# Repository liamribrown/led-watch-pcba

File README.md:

# LED analogue watch PCBA

A wristwatch board that shows the time like an analogue watch, with LEDs in place of hands.
It stays dark until you press a button or tilt your wrist, then shows the time for about 5 seconds.

- **Board:** round, 38 mm, 4 layers, 1.0 mm. 60 amber 0402 LEDs on the outer ring (minutes) and
  12 red 0603 LEDs on the inner ring (hours), charlieplexed from 9 pins of an ATtiny3217.
  CR2032 coin cell, 32.768 kHz crystal for the clock, LIS2DH12 accelerometer for tilt-to-wake,
  two side buttons. Designed in KiCad 9 and generated from Python.
- **Firmware:** C for the ATtiny3217 (the pin-compatible ATtiny1617 also fits), with host unit tests.
- **Simulator:** a 3D model of the board plus a working watch that runs the real firmware logic
  compiled to WebAssembly: https://ai.liambrown.uk/watch/

## Status

Designed and reviewed on paper, **not yet built or tested on hardware.** Don't order boards
you aren't prepared to debug. Open points are in `projects/led-watch/SPEC.md` ("As built" and
the review tables at the end) and in `docs/reviews/`.

## Layout

| Path | What |
|---|---|
| `projects/led-watch/SPEC.md` | Requirements, decisions, as-built notes, BOM with LCSC parts |
| `projects/led-watch/PINMAP.md` | Pin map and LED table (the source of truth for firmware) |
| `projects/led-watch/tools/` | Python that generates the schematic and board (`generate.py`), plus the coin-cell safety check |
| `projects/led-watch/led-watch.kicad_*` | Generated KiCad project |
| `projects/led-watch/export.sh` | ERC/DRC gate, then gerbers, JLCPCB BOM and placement files |
| `projects/led-watch/firmware/` | Firmware, tests, build and flash scripts (see its README) |
| `projects/watch-sim/` | The browser simulator |
| `docs/led-watch-schematic.pdf` | Schematic (A3, one sheet, generated from the KiCad file) |
| `docs/reviews/` | Independent design reviews of the spec and board |

## Build it

```bash
# Board: needs KiCad 9 (kicad-cli). Stops on any ERC/DRC or coin-cell check failure.
projects/led-watch/export.sh

# Firmware: needs gcc (host tests) and avr-gcc.
cd projects/led-watch/firmware && ./build.sh
```

## Notes

- **Coin cell:** the board has a copper keep-out under the cell, enforced by
  `tools/check_cell.py`. Order plugged (filled) vias. 3.3 V SerialUPDI adapters only: a 5 V one
  would push current into the cell. In a case, the cell should only be reachable with a tool.
- **Cost (JLCPCB quote, 2026-11-12):** 10 assembled boards, both sides, about US$231 before
  shipping. Check part rotations in JLCPCB's placement preview before paying.
- **Stock:** the ATtiny3217 and the B3U-3100P buttons were low in stock on LCSC when the BOM
  was checked. The ATtiny1617 is the fallback chip.
- The documents were written by a small team of AI agents working under one person's direction,
  so they refer to "000" (the human) and agent numbers (003 Hardware, 004 Firmware, 007 Review).

## Licence

Software (firmware, simulator, generator scripts): **MIT**. Hardware design and documents:
**CERN-OHL-P-2.0**. Which folder is which is in [`LICENSE`](LICENSE); the texts are in `LICENSES/`.

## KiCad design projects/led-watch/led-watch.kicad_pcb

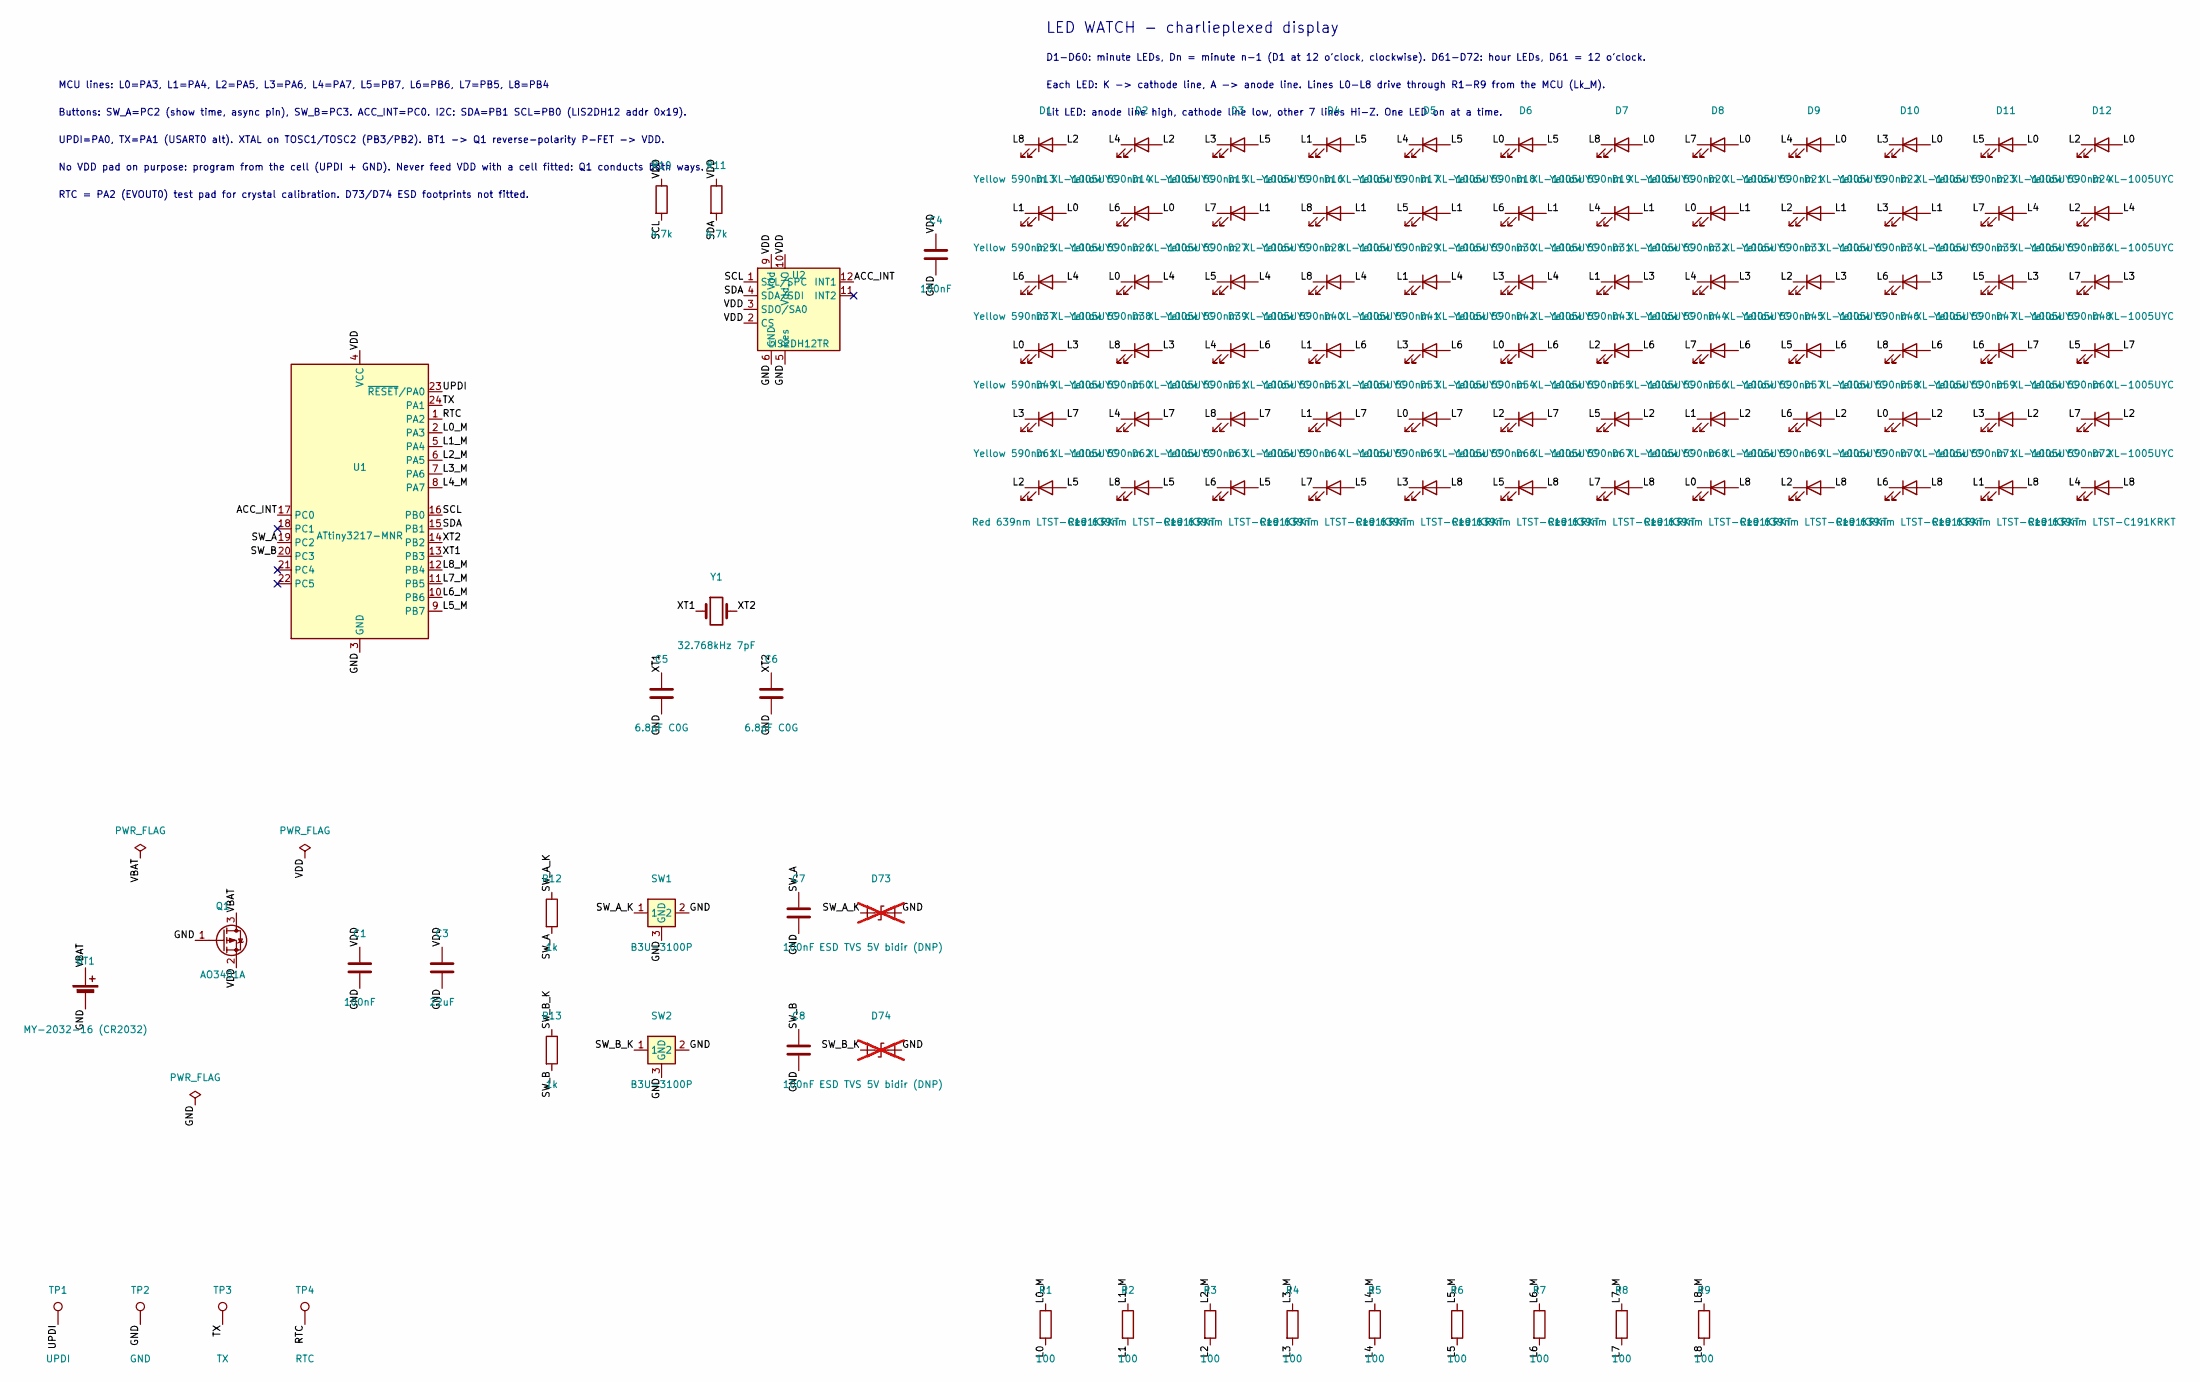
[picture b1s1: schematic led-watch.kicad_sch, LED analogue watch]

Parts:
BT1: MY-2032-16 (CR2032); BatteryHolder_MYOUNG_MY-2032-16; LCSC C2902340
C1, C4, C7, C8: 100nF; C_0402_1005Metric; LCSC C1525
C3: 22uF; C_0805_2012Metric; LCSC C45783
C5, C6: 6.8pF C0G; C_0402_1005Metric; LCSC C1576
D1, D2, D3, D4, D5, D6, D7, D8, D9, D10, D11, D12, D13, D14, D15, D16, D17, D18, D19, D20, D21, D22, D23, D24, D25, D26, D27, D28, D29, D30, D31, D32, D33, D34, D35, D36, D37, D38, D39, D40, D41, D42, D43, D44, D45, D46, D47, D48, D49, D50, D51, D52, D53, D54, D55, D56, D57, D58, D59, D60: Yellow 590nm XL-1005UYC; LED_0402_1005Metric_Tight; LCSC C25503856
D61, D62, D63, D64, D65, D66, D67, D68, D69, D70, D71, D72: Red 639nm LTST-C191KRKT; LED_0603_1608Metric; LCSC C125099
D73, D74: ESD TVS 5V bidir (DNP); D_0402_1005Metric; not fitted
Q1: AO3401A; SOT-23; LCSC C15127
R1, R2, R3, R4, R5, R6, R7, R8, R9: 100; R_0402_1005Metric; LCSC C25076
R10, R11: 4.7k; R_0402_1005Metric; LCSC C25900
R12, R13: 1k; R_0402_1005Metric; LCSC C11702
SW1, SW2: B3U-3100P; SW_SPST_B3U-3100P; LCSC C6748648
TP1: UPDI; TestPoint_Pad_D1.0mm
TP2: GND; TestPoint_Pad_D1.0mm
TP3: TX; TestPoint_Pad_D1.0mm
TP4: RTC; TestPoint_Pad_D1.0mm
U1: ATtiny3217-MNR; QFN-24-1EP_4x4mm_P0.5mm_EP2.6x2.6mm; LCSC C614177
U2: LIS2DH12TR; LGA-12_2x2mm_P0.5mm; LCSC C110926
Y1: 32.768kHz 7pF; Crystal_SMD_2012-2Pin_2.0x1.2mm; LCSC C5136974

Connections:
/ACC_INT: U1.17 (PC0), U2.12 (INT1)
/GND: BT1.2 (-), C1.2, C3.2, C4.2, C5.2, C6.2, C7.2, C8.2, D73.2 (A2), D74.2 (A2), Q1.1 (G), SW1.2, SW1.3 (GND), SW2.2, SW2.3 (GND), TP2.1, U1.3 (GND), U1.25 (GND), U2.5 (Res), U2.6 (GND), U2.7 (GND), U2.8 (GND)
/L0: D6.1 (K), D7.2 (A), D8.2 (A), D9.2 (A), D10.2 (A), D11.2 (A), D12.2 (A), D13.2 (A), D14.2 (A), D20.1 (K), D26.1 (K), D37.1 (K), D42.1 (K), D53.1 (K), D58.1 (K), D68.1 (K), R1.2
/L0_M: R1.1, U1.2 (PA3)
/L1: D4.1 (K), D13.1 (K), D15.2 (A), D16.2 (A), D17.2 (A), D18.2 (A), D19.2 (A), D20.2 (A), D21.2 (A), D22.2 (A), D29.1 (K), D31.1 (K), D40.1 (K), D52.1 (K), D56.1 (K), D71.1 (K), R2.2
/L1_M: R2.1, U1.5 (PA4)
/L2: D1.2 (A), D2.2 (A), D12.1 (K), D21.1 (K), D24.1 (K), D33.1 (K), D43.1 (K), D54.1 (K), D55.2 (A), D56.2 (A), D57.2 (A), D58.2 (A), D59.2 (A), D60.2 (A), D61.1 (K), D69.1 (K), R3.2
/L2_M: R3.1, U1.6 (PA5)
/L3: D3.1 (K), D10.1 (K), D22.1 (K), D30.1 (K), D31.2 (A), D32.2 (A), D33.2 (A), D34.2 (A), D35.2 (A), D36.2 (A), D37.2 (A), D38.2 (A), D41.1 (K), D49.1 (K), D59.1 (K), D65.1 (K), R4.2
/L3_M: R4.1, U1.7 (PA6)
/L4: D2.1 (K), D5.1 (K), D9.1 (K), D19.1 (K), D23.2 (A), D24.2 (A), D25.2 (A), D26.2 (A), D27.2 (A), D28.2 (A), D29.2 (A), D30.2 (A), D32.1 (K), D39.1 (K), D50.1 (K), D72.1 (K), R5.2
/L4_M: R5.1, U1.8 (PA7)
/L5: D3.2 (A), D4.2 (A), D5.2 (A), D6.2 (A), D11.1 (K), D17.1 (K), D27.1 (K), D35.1 (K), D45.1 (K), D48.1 (K), D55.1 (K), D61.2 (A), D62.2 (A), D63.2 (A), D64.2 (A), D66.1 (K), R6.2
/L5_M: R6.1, U1.9 (PB7)
/L6: D14.1 (K), D18.1 (K), D25.1 (K), D34.1 (K), D39.2 (A), D40.2 (A), D41.2 (A), D42.2 (A), D43.2 (A), D44.2 (A), D45.2 (A), D46.2 (A), D47.1 (K), D57.1 (K), D63.1 (K), D70.1 (K), R7.2
/L6_M: R7.1, U1.10 (PB6)
/L7: D8.1 (K), D15.1 (K), D23.1 (K), D36.1 (K), D44.1 (K), D47.2 (A), D48.2 (A), D49.2 (A), D50.2 (A), D51.2 (A), D52.2 (A), D53.2 (A), D54.2 (A), D60.1 (K), D64.1 (K), D67.1 (K), R8.2
/L7_M: R8.1, U1.11 (PB5)
/L8: D1.1 (K), D7.1 (K), D16.1 (K), D28.1 (K), D38.1 (K), D46.1 (K), D51.1 (K), D62.1 (K), D65.2 (A), D66.2 (A), D67.2 (A), D68.2 (A), D69.2 (A), D70.2 (A), D71.2 (A), D72.2 (A), R9.2
/L8_M: R9.1, U1.12 (PB4)
/RTC: TP4.1, U1.1 (PA2)
/SCL: R10.2, U1.16 (PB0), U2.1 (SCL/SPC)
/SDA: R11.2, U1.15 (PB1), U2.4 (SDA/SDI)
/SW_A: C7.1, R12.2, U1.19 (PC2)
/SW_A_K: D73.1 (A1), R12.1, SW1.1
/SW_B: C8.1, R13.2, U1.20 (PC3)
/SW_B_K: D74.1 (A1), R13.1, SW2.1
/TX: TP3.1, U1.24 (PA1)
/UPDI: TP1.1, U1.23 (~RESET/PA0)
/VBAT: BT1.1 (+), Q1.3 (D)
/VDD: C1.1, C3.1, C4.1, Q1.2 (S), R10.1, R11.1, U1.4 (VCC), U2.2 (CS), U2.3 (SDO/SA0), U2.9 (Vdd), U2.10 (Vdd_IO)
/XT1: C5.1, U1.13 (PB3), Y1.1
/XT2: C6.1, U1.14 (PB2), Y1.2

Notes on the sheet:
LED WATCH - charlieplexed display
D1-D60: minute LEDs, Dn = minute n-1 (D1 at 12 o'clock, clockwise). D61-D72: hour LEDs, D61 = 12 o'clock.
Each LED: K -> cathode line, A -> anode line. Lines L0-L8 drive through R1-R9 from the MCU (Lk_M).
Lit LED: anode line high, cathode line low, other 7 lines Hi-Z. One LED on at a time.
MCU lines: L0=PA3, L1=PA4, L2=PA5, L3=PA6, L4=PA7, L5=PB7, L6=PB6, L7=PB5, L8=PB4
Buttons: SW_A=PC2 (show time, async pin), SW_B=PC3. ACC_INT=PC0. I2C: SDA=PB1 SCL=PB0 (LIS2DH12 addr 0x19).
UPDI=PA0, TX=PA1 (USART0 alt). XTAL on TOSC1/TOSC2 (PB3/PB2). BT1 -> Q1 reverse-polarity P-FET -> VDD.
No VDD pad on purpose: program from the cell (UPDI + GND). Never feed VDD with a cell fitted: Q1 conducts both ways.
RTC = PA2 (EVOUT0) test pad for crystal calibration. D73/D74 ESD footprints not fitted.

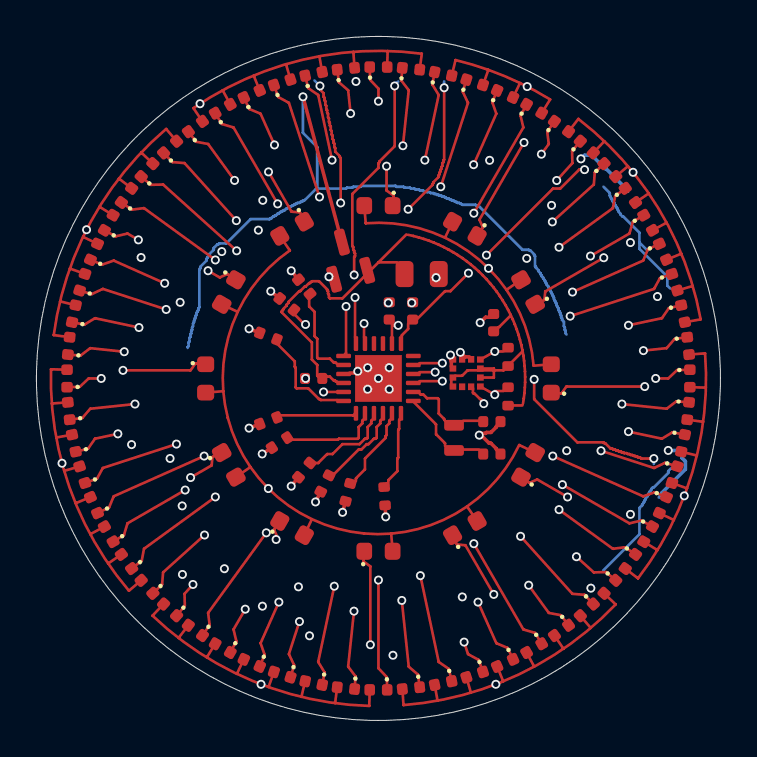
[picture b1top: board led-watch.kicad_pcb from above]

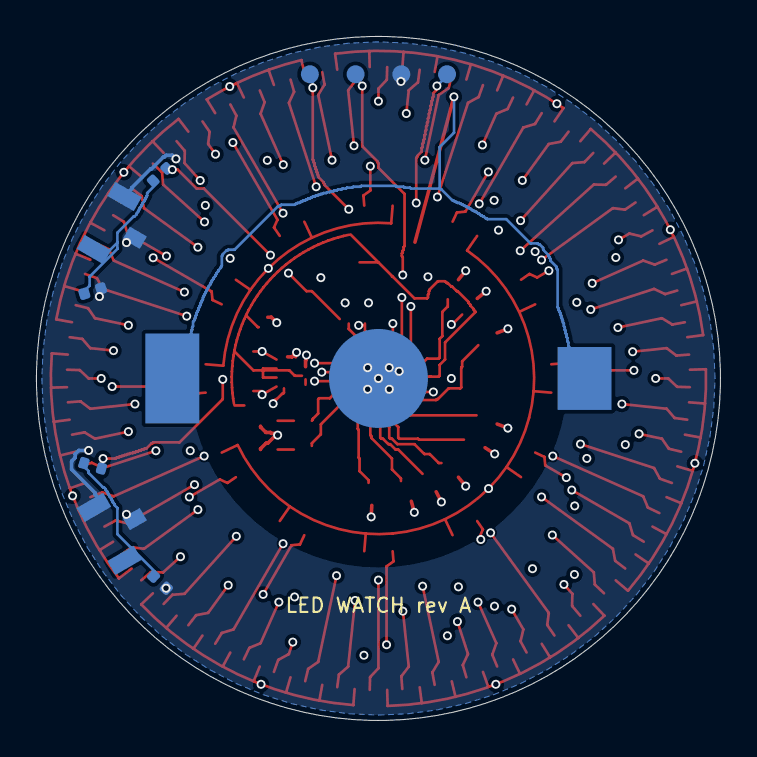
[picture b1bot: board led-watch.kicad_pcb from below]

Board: 4 copper layers, 38.0 x 38.0 mm, 105 parts (11 on the bottom side), 33 nets.

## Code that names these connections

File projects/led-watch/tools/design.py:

"""LED watch: design data shared by the schematic and PCB generators.

Everything electrical lives here: parts, LCSC numbers, pin-to-net maps, and the
charlieplex LED assignment. generate.py turns it into KiCad files.
"""
import math
import random

# ---------------------------------------------------------------- parts / LCSC
# LCSC numbers and stock were checked on lcsc.com on 2026-11-11 (see SPEC.md / BOM).
P = {
    "MCU":   dict(value="ATtiny3217-MNR", lcsc="C614177", fp="Package_DFN_QFN:QFN-24-1EP_4x4mm_P0.5mm_EP2.6x2.6mm"),
    "ACC":   dict(value="LIS2DH12TR", lcsc="C110926", fp="Package_LGA:LGA-12_2x2mm_P0.5mm"),
    "XTAL":  dict(value="32.768kHz 7pF", lcsc="C5136974", fp="Crystal:Crystal_SMD_2012-2Pin_2.0x1.2mm"),
    "FET":   dict(value="AO3401A", lcsc="C15127", fp="Package_TO_SOT_SMD:SOT-23"),
    "BAT":   dict(value="MY-2032-16 (CR2032)", lcsc="C2902340", fp="led-watch:BatteryHolder_MYOUNG_MY-2032-16"),
    "SW":    dict(value="B3U-3100P", lcsc="C6748648", fp="Button_Switch_SMD:SW_SPST_B3U-3100P"),
    "LED_M": dict(value="Yellow 590nm XL-1005UYC", lcsc="C25503856", fp="led-watch:LED_0402_1005Metric_Tight"),
    "LED_H": dict(value="Red 639nm LTST-C191KRKT", lcsc="C125099", fp="LED_SMD:LED_0603_1608Metric"),
    "R100":  dict(value="100", lcsc="C25076", fp="Resistor_SMD:R_0402_1005Metric"),
    "R4k7":  dict(value="4.7k", lcsc="C25900", fp="Resistor_SMD:R_0402_1005Metric"),
    "C100n": dict(value="100nF", lcsc="C1525", fp="Capacitor_SMD:C_0402_1005Metric"),
    "C6p8":  dict(value="6.8pF C0G", lcsc="C1576", fp="Capacitor_SMD:C_0402_1005Metric"),
    "C10u":  dict(value="10uF", lcsc="C19702", fp="Capacitor_SMD:C_0603_1608Metric"),
    "C22u":  dict(value="22uF", lcsc="C45783", fp="Capacitor_SMD:C_0805_2012Metric"),
    "TP":    dict(value="TP", lcsc="", fp="TestPoint:TestPoint_Pad_D1.0mm"),
    "R1k":   dict(value="1k", lcsc="C11702", fp="Resistor_SMD:R_0402_1005Metric"),
    "TVS":   dict(value="ESD TVS 5V bidir (DNP)", lcsc="", fp="Diode_SMD:D_0402_1005Metric"),
}

N_LINES = 9                      # charlieplex lines L0..L8 -> 9*8 = 72 LEDs

# ATtiny3217 VQFN-24 pin -> net. Pin numbers/functions from the datasheet I/O
# multiplexing table (TOSC1=PB3, TOSC2=PB2, SDA=PB1, SCL=PB0, UPDI=PA0, TxD alt=PA1).
MCU_PINS = {
    "1": "RTC",    # PA2 = EVOUT0: RTC/PIT event out to a test pad for crystal calibration
    "2": "L0_M",   # PA3
    "3": "GND",
    "4": "VDD",
    "5": "L1_M",   # PA4
    "6": "L2_M",   # PA5
    "7": "L3_M",   # PA6
    "8": "L4_M",   # PA7
    "9": "L5_M",   # PB7
    "10": "L6_M",  # PB6
    "11": "L7_M",  # PB5
    "12": "L8_M",  # PB4
    "13": "XT1",   # PB3 TOSC1
    "14": "XT2",   # PB2 TOSC2
    "15": "SDA",   # PB1
    "16": "SCL",   # PB0
    "17": "ACC_INT",  # PC0
    "18": None,    # PC1 spare
    "19": "SW_A",  # PC2 (fully async pin: any edge wakes from any sleep)
    "20": "SW_B",  # PC3 (use BOTHEDGES/LEVEL sense to wake from standby)
    "21": None, "22": None,   # PC4, PC5 spare
    "23": "UPDI",  # PA0
    "24": "TX",    # PA1 (USART0 TxD, alternate position)
    "25": "GND",   # exposed pad
}
MCU_PORTPIN = {"1": "PA2", "2": "PA3", "5": "PA4", "6": "PA5", "7": "PA6", "8": "PA7",
               "9": "PB7", "10": "PB6", "11": "PB5", "12": "PB4", "19": "PC2", "20": "PC3", "17": "PC0",
               "15": "PB1", "16": "PB0", "13": "PB3", "14": "PB2", "23": "PA0", "24": "PA1",
               "18": "PC1", "21": "PC4", "22": "PC5"}

# LIS2DH12 (datasheet Table 2). SDO/SA0 has an internal pull-up: tie it HIGH,
# tying it low would waste ~100 uA. CS high selects I2C. Address = 0x19.
ACC_PINS = {"1": "SCL", "2": "VDD", "3": "VDD", "4": "SDA", "5": "GND", "6": "GND",
            "7": "GND", "8": "GND", "9": "VDD", "10": "VDD", "11": None, "12": "ACC_INT"}

# ---------------------------------------------------------------- LED geometry
# Clock positions: minute m at 6*m degrees, hour h at 30*h degrees (clockwise from 12).
TAB_MINUTES = set(range(13, 18)) | set(range(43, 48))   # coin-cell tabs under these
BUTTON_MINUTES = {10, 20}                                # B3U ground pad under these
MIN_BLOCK_START = 6


def ring_ok(m, c):
    """Can a cathode via on ring c sit in minute sector m? (see generate.py geometry)"""
    if m in TAB_MINUTES and c < 5:
        return False          # via would hit the battery-holder tab on B.Cu
    if m in BUTTON_MINUTES and c > 6:
        return False          # via would hit the switch ground pad on B.Cu
    return True


def assign_leds(seed=7):
    """Return (minute_leds, hour_leds) as dicts index -> (anode_line, cathode_line).

    Blocks of 8 LEDs share an anode line, so their anodes join with one copper arc
    and every LED needs only one via (for its cathode). Blocks 0..6 are minutes
    6..61 (mod 60), block 7 is minutes 2..5 + hours 0..3, block 8 is hours 4..11.
    """
    rnd = random.Random(seed)
    blocks = [[("m", (MIN_BLOCK_START + 8 * b + i) % 60) for i in range(8)] for b in range(7)]
    blocks.append([("m", m) for m in (2, 3, 4, 5)] + [("h", h) for h in (0, 1, 2, 3)])
    blocks.append([("h", h) for h in range(4, 12)])
    for _ in range(20000):
        anodes = list(range(N_LINES))
        rnd.shuffle(anodes)
        res_m, res_h, ok = {}, {}, True
        # minutes first (hours must avoid the minute cathode in the same sector)
        order = sorted(range(9), key=lambda b: any(k == "h" for k, _ in blocks[b]))
        for b in order:
            a = anodes[b]
            cath = [c for c in range(N_LINES) if c != a]
            leds = blocks[b]

            def ok_for(kind, idx, c):
                if kind == "m":
                    return ring_ok(idx, c)
                m = 5 * idx
                return ring_ok(m, c) and res_m.get(m, (None, None))[1] != c

            # backtracking assignment of the 8 cathodes in this block
            sol = [None] * 8

            def bt(i, free):
                if i == 8:
                    return True
                kind, idx = leds[i]
                opts = [c for c in free if ok_for(kind, idx, c)]
                rnd.shuffle(opts)
                for c in opts:
                    sol[i] = c
                    if bt(i + 1, free - {c}):
                        return True
                return False

            if not bt(0, frozenset(cath)):
                ok = False
                break
            for (kind, idx), c in zip(leds, sol):
                (res_m if kind == "m" else res_h)[idx] = (a, c)
        if ok:
            return res_m, res_h, anodes, blocks
    raise RuntimeError("no LED assignment found")


if __name__ == "__main__":
    m, h, anodes, blocks = assign_leds()
    print("block anodes:", anodes)
    for i in range(60):
        print(f"minute {i:2d}: anode L{m[i][0]} cathode L{m[i][1]}")
    for i in range(12):
        print(f"hour   {i:2d}: anode L{h[i][0]} cathode L{h[i][1]}")
